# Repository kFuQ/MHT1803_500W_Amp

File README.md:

# 500W RF Power Amplifier Design

A professional-grade 500W RF power amplifier design featuring comprehensive protection, monitoring, and control systems. Built around the MHT1803 LDMOS transistor pair in a push-pull configuration.

## Key Specifications

- Output Power: 500W continuous
- Frequency Range: 1.8-30 MHz
- Primary Input: 12-13.8VDC @ 50A
- Efficiency: >65% typical
- Input Power: 0-5W adjustable
- VSWR Protection: Auto-shutdown at 3:1
- Thermal Protection: 85°C shutdown, 75°C resume
- Monitoring: Input power, output power, temperature, current

## Power System Architecture

### Main Power Input
- Operating Voltage: 12-13.8VDC nominal
- Maximum Current: 50A continuous, 55A peak
- Input Connection: 
  - Anderson Powerpole 75A connectors (Red/Black)
  - Reverse polarity protection diode
- Input Filtering:
  - 4x 2200µF low-ESR capacitors
  - Common-mode choke (FT240-43 core)
  - 100nF ceramic bypass capacitors
  - MOV surge protection

### DC-DC Conversion Stage
- Primary Converter:
  - Synchronous buck-boost topology
  - IR2110 gate drivers
  - IRFP260N MOSFETs (4 pairs)
  - Operating frequency: 125kHz
  - Efficiency: >92% at full load
  - Output: 50V @ 15A
- Transformer Design:
  - Core: 2x FT240-43 stacked
  - Primary: 4T #12 AWG bifilar
  - Secondary: 16T #16 AWG bifilar
  - Interleaved winding for lower leakage
  - Epoxy potted for stability
- Output Filtering:
  - 2x 470µH inductors (T200-2 cores)
  - 4x 220µF/100V capacitors
  - 100nF/100V ceramic bypass
  - Common-mode rejection filter

### Power Distribution
- Main RF Stage (+50VDC):
  - Independent thermal monitoring
  - Isolated feedback paths
  - Current limiting at 16A
- Control Circuits (12VDC direct):
  - Relay coil drivers
  - Fan control circuits
  - LED indicators
  - Input protection circuits
- Logic Circuits (5VDC regulated):
  - LM2596 switching regulator
  - 2A maximum output
  - Temperature compensated
  - Short circuit protected

### Power Monitoring System
- Input Monitoring:
  - Hall-effect current sensor (ACS758-050B)
  - Voltage divider with op-amp buffer
  - Temperature compensation
  - 12-bit ADC sampling
- DC-DC Converter Monitoring:
  - Output voltage (±1% precision)
  - Output current (ACS712-30A)
  - Heatsink temperature (LM35)
  - Transformer temperature (NTC)
  - Efficiency calculation
- Protection Thresholds:
  - Input under-voltage: <11.0V
  - Input over-voltage: >15.0V
  - Input current: >55A
  - Output voltage: >52V
  - Temperature: >85°C

### Protection Mechanisms
- Input Protection:
  - Reverse polarity (60V/60A Schottky)
  - Over-current (60A blade fuse)
  - Surge protection (30V MOV)
  - EMI filtering (common mode)
- DC-DC Protection:
  - Soft-start ramping (2 seconds)
  - Over-temperature shutdown
  - Current limiting (fold-back)
  - Short circuit protection
  - Output crowbar (SCR based)
- Backup Systems:
  - Emergency shutdown circuit
  - Watchdog timer reset
  - Fault condition memory
  - Multiple redundant protections

### Power Control Interface
- Front Panel:
  - Digital ammeter (input current)
  - Digital voltmeter (input voltage)
  - Power status LEDs
  - Temperature indication
  - Fault status display

### Cooling System
- CPU Liquid Cooling:
  - 240mm AIO (All-In-One) CPU cooler
  - Custom copper mounting plate for LDMOS pair
  - Arctic Silver 5 thermal compound
  - Integrated pump and radiator
  - Temperature sensor in coolant loop
- Thermal Management:
  - Direct die contact cooling
  - Coolant temperature monitoring
  - Flow detection
  - Pump speed monitoring
  - Emergency shutdown on pump failure
- Heatsink Interface:
  - Material: Copper base plate
  - Size: Matched to LDMOS package
  - Thermal resistance: <0.1°C/W
  - Mounting: Arctic Silver 5 thermal compound
  - Temperature monitoring via NTC

## System Architecture

### RF Input Section
- Dual input connectors (SO-239 and SMA)
- Input relay switching with LED status
- Pi-network attenuator (100Ω/1W, 150Ω/1W)
- TVS diode protection (SMBJ12CA)
- 7-element low-pass filter (35MHz)
- AD8307 power monitoring (-75 to +17 dBm)
- RF power sampling (-30dB directional coupler)
- 5-50pF impedance trimmer
- CD4538 relay control (10ms debounce)
- Input VSWR bridge (PDC10-1)
- Power meter calibration points
- RF isolation network
- Ground plane segmentation

### RF Amplifier Core
- MHT1803 LDMOS transistor pair
- 10pF neutralization capacitors
- 47Ω gate stopper resistors
- Bypass capacitors:
  - Drain: 100nF + 10µF
  - Source: 100nF
- Pi-network matching:
  - Input: L=2.2µH, C=100pF
  - Output: L=3.3µH, C=220pF
- FB-43-801 ferrite beads
- Gate bias monitoring points
- 0.1Ω current sensing
- 10Ω/2W anti-parasitic resistors
- 40MHz harmonic trap
- FT240-43 4:1 balun
- Temperature compensation
- ESD protection
- Thermal management:
  - Heatsink: 0.1°C/W
  - Arctic Silver 5 compound
  - Thermal monitoring
  - PCB thermal relief

### Protection Circuits
- Voltage monitoring (LM339):
  - +50V main supply
  - +12V control supply
  - +5V logic supply
- Watchdog timer (555-based)
- PDC10-1 RF detector
- 8-LED fault display
- Manual reset
- 2-second startup delay
- Cooling system:
  - YF-S201 flow sensor
  - Three LM35 sensors
  - ACS712-30A current monitoring
- Fault management:
  - CD4043B latching
  - Priority encoding

## Additional Features

### Thermal Management
- Copper base heatsink with aluminum fins
- Thermal resistance: 0.1°C/W
- Size: 200x150x60mm
- Arctic Silver 5 thermal compound
- Three LM35 temperature sensors
- YF-S201 coolant flow sensor
- Thermal shutdown protection
- PCB thermal relief design

### User Interface
- 2-digit 7-segment fault display
- 8 status LED indicators:
  - Power status
  - Protection active
  - Temperature warning
  - VSWR warning
  - Band indicators (3 LEDs)
  - Fault indicator
- Reset pushbutton
- Mode selection switch
- Band selection control
- Power output adjustment

### EMI/RFI Protection
- Multi-layer PCB with ground planes
- RF shielding compartments
- Ferrite beads on DC lines
- Feed-through capacitors
- Common-mode chokes
- TVS diode protection
- Isolated ground planes
- EMI-suppressed enclosure

### PCB Specifications
- Material: Rogers RO4350B
- Thickness: 0.762mm
- Copper: 2oz
- Min trace: 0.3mm
- Thermal vias: 0.3mm @ 1mm spacing
- Ground planes:
  - RF section isolation
  - Digital section separation
  - Power supply star point
  - 5mm via stitching

## Recent Updates
1. RF Input Section:
   - Added power meter calibration
   - Implemented RF isolation
   - Added relay protection
   - Enhanced VSWR monitoring
   - Improved grounding scheme

2. RF Amplifier Core:
   - Added temperature compensation
   - Enhanced heatsink mounting
   - Updated PCB specifications

3. Protection Circuits:
   - Added fault display system
   - Enhanced watchdog system
   - Improved isolation
   - Added priority encoding

## 📑 Documentation
- [User Manual](./MHT1803_Amplifier_500W_User_Manual.pdf)
- [Compliance Summary](./MHT1803_Amplifier_500W.ComplianceSummary.md) - KiCad 9.0.2 compliance analysis and project status
- [Bill of Materials](./MHT1803_Amplifier_500W.BOM.csv)
- [Repair Guide](./MHT1803_Amplifier_500W_Repair_Diagram.svg)
- [Verification Report](./MHT1803_Amplifier_500W_VERIFICATION_REPORT.md)
- [File List](./MHT1803_Amplifier_500W.FileList.md)

## Safety Features
- Multiple thermal sensors
- Current limiting
- VSWR protection
- Voltage monitoring
- Emergency shutdown
- Status indicators

## License
Copyright © 2025 kFuQ
All rights reserved.

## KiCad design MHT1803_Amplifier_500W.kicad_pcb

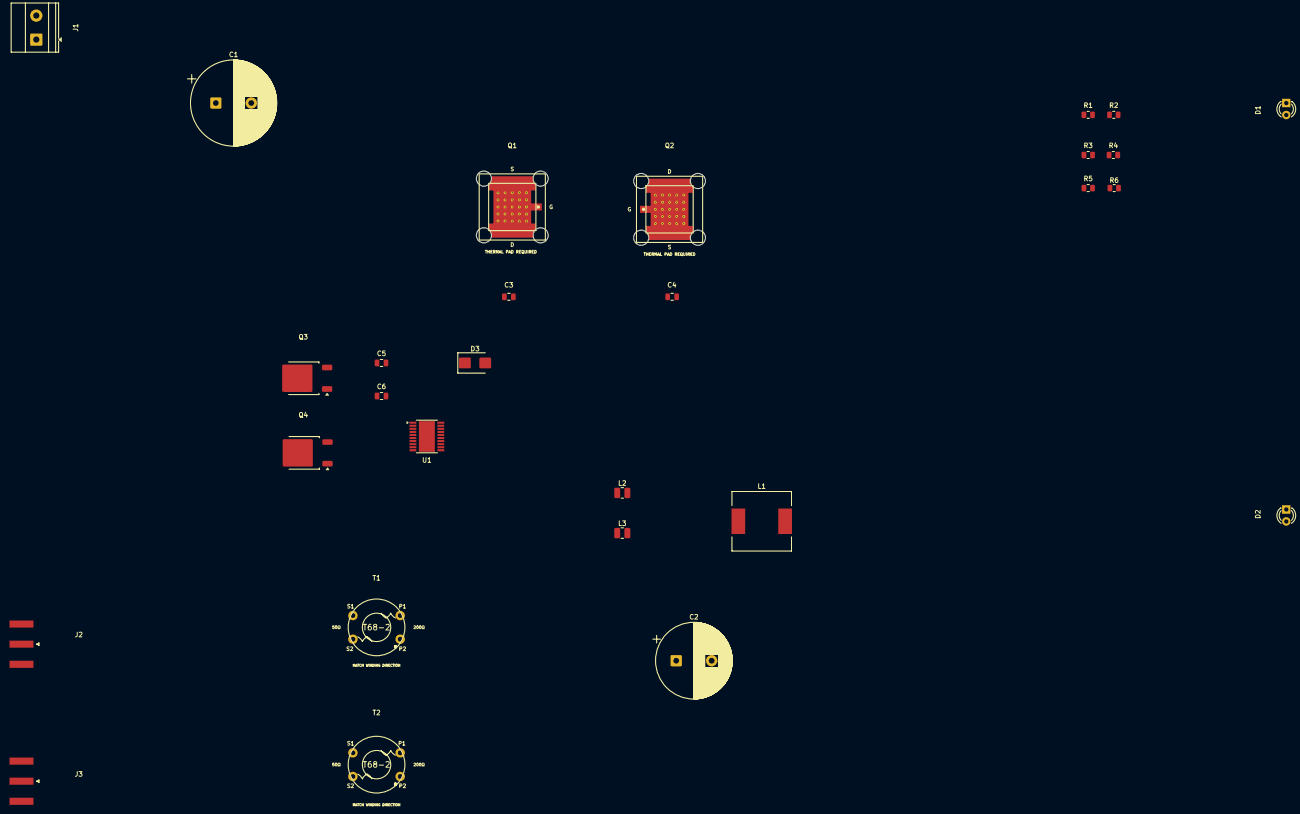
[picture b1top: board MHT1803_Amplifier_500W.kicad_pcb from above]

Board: 2 copper layers, 28 parts (0 on the bottom side), 6 nets, no tracks yet.

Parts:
C1: 1000µF; CP_Radial_D18.0mm_P7.50mm
C2: 470µF; CP_Radial_D16.0mm_P7.50mm
C3, C4, C5: 1nF; C_0805_2012Metric
C6: 100nF; C_0805_2012Metric
D1: PWR_LED_GREEN; LED_D3.0mm
D2: OVHT_LED_RED; LED_D3.0mm
D3: MBRS340; D_SMB
J1: POWER_12V; TerminalBlock_Phoenix_MKDS-1,5-2-5.08_1x02_P5.08mm_Horizont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
J2: SO239_INPUT; SMA_Amphenol_132289_EdgeMount
J3: SO239_OUTPUT; SMA_Amphenol_132289_EdgeMount
L1: 100µH; L_12x12mm_H8mm
L2, L3: 22nH; L_1008_2520Metric
Q1, Q2: MHT1803; MHT1803_M244
Q3, Q4: SI7336ADP; TO-252-2
R1, R2: 10Ω; R_0805_2012Metric
R3, R4: 1K; R_0805_2012Metric
R5: 10K; R_0805_2012Metric
R6: 2.2K; R_0805_2012Metric
T1, T2: RF_Transformer_4to1; RF_Transformer_T68
U1: LM25122MY; HTSSOP-20-1EP_4.4x6.5mm_P0.65mm_EP3.4x6.5mm

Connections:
+12V: Q3.2 (D), Q4.3 (S), U1.7 (PGND)
unnamed: D3.2 (A), U1.5 (LO2)
unnamed: C6.1, D3.1 (K), Q3.3 (S), Q4.2 (D)
unnamed: C3.1, Q1.3 (D)
unnamed: C4.1, Q2.2 (S)
unnamed: C6.2, U1.4 (LO1)

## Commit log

2025-06-14 fixed errors
2025-06-14 verified circuit
2025-06-15 split schematics to smaller, separate files per section
2025-06-15 deleted old files
2025-06-15 updated README - removed parts that dont exist in the design
2025-06-15 removed features that don't exist in the design in the README
2025-06-15 added gitignore
2025-06-15 added manual build script to make pdf from tex (Uses MikTex)
2025-06-15 updated compliance doc
2025-06-15 fixed broken links in README
